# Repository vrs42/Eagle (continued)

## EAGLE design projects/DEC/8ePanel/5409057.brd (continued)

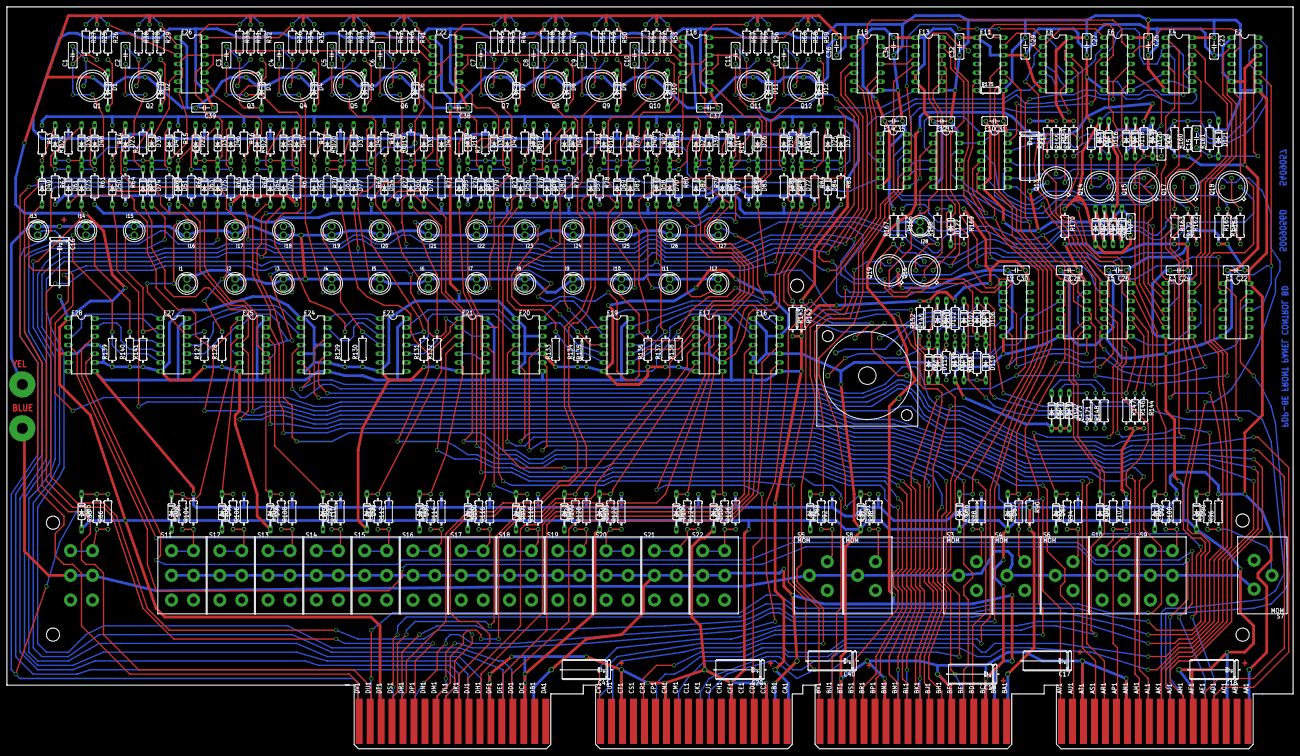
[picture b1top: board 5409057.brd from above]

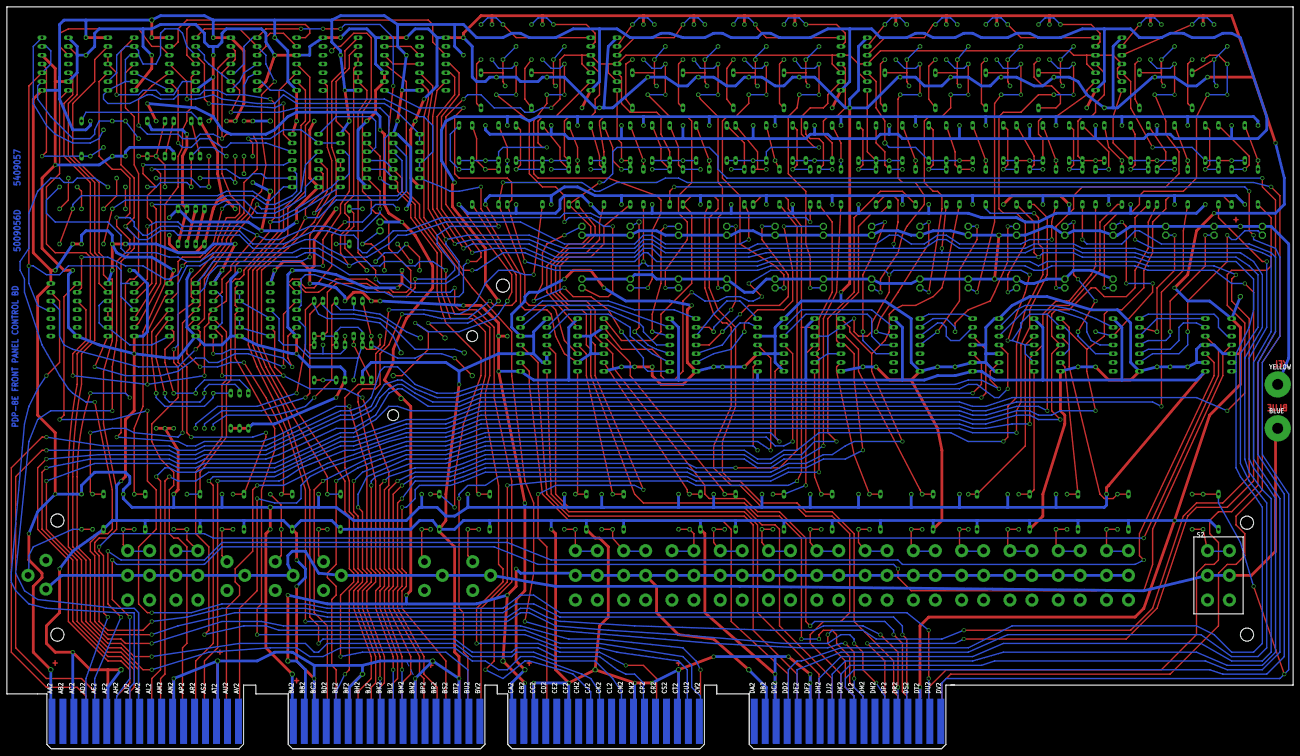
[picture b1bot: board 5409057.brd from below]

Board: 4 copper layers, 372.1 x 214.6 mm, 445 parts (3 on the bottom side), 319 nets.

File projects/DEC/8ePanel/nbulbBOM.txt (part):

Partlist exported from C:/Users/vrs/Documents/Eagle/projects/DEC/8ePanel/nbulb.sch at 6/27/2019 12:56:02 AM

Qty Value    Device            Package      Parts                                                                                                                                                                                                                                                                                                                                                                                                                                                                                                                                                                                          Description                                      
1            QUAD              EDGE-CON8    U$2                                                                                                                                                                                                                                                                                                                                                                                                                                                                                                                                                                                            Quad-Height DEC board                            
19  .01uF    C-US050-025X075   C050-025X075 C21, C22, C23, C24, C25, C26, C27, C28, C29, C30, C31, C32, C33, C34, C35, C36, C37, C38, C39                                                                                                                                                                                                                                                                                                                                                                                                                                                                                                  CAPACITOR, American symbol                       
22  1.5K     R-US_0207/10      0207/10      R85, R86, R87, R89, R91, R93, R95, R97, R99, R101, R103, R105, R107, R109, R111, R113, R115, R117, R119, R121, R123, R125                                                                                                                                                                                                                                                                                                                                                                                                                                                                      RESISTOR, American symbol                        
2   100      R-US_0207/10      0207/10      R154, R169                                                                                                                                                                                                                                                                                                                                                                                                                                                                                                                                                                                     RESISTOR, American symbol                        
1   150      R-US_0207/10      0207/10      R156                                                                                                                                                                                                                                                                                                                                                                                                                                                                                                                                                                                           RESISTOR, American symbol                        
15  15K      R-US_0207/10      0207/10      R1, R2, R3, R4, R5, R6, R7, R8, R9, R10, R11, R12, R158, R159, R160                                                                                                                                                                                                                                                                                                                                                                                                                                                                                                                            RESISTOR, American symbol                        
1   1800     R-US_0207/10      0207/10      R161                                                                                                                                                                                                                                                                                                                                                                                                                                                                                                                                                                                           RESISTOR, American symbol                        
6   1K       R-US_0207/10      0207/10      R149, R150, R153, R155, R166, R168                                                                                                                                                                                                                                                                                                                                                                                                                                                                                                                                                             RESISTOR, American symbol                        
2   1N4153   1N4148DO35-10     DO35-10      D120, D130                                                                                                                                                                                                                                                                                                                                                                                                                                                                                                                                                                                     DIODE                                            
114 1N4154   1N4148DO35-10     DO35-10      D1, D2, D3, D4, D5, D6, D7, D8, D9, D10, D11, D12, D13, D14, D15, D16, D17, D18, D19, D20, D21, D22, D23, D24, D25, D26, D27, D28, D29, D30, D31, D32, D33, D34, D35, D36, D37, D38, D39, D40, D41, D42, D43, D44, D45, D46, D47, D48, D49, D50, D51, D52, D53, D54, D55, D56, D57, D58, D59, D60, D61, D62, D63, D64, D65, D66, D67, D68, D69, D70, D71, D72, D73, D74, D75, D76, D77, D78, D79, D80, D81, D82, D83, D84, D85, D86, D87, D88, D89, D90, D91, D92, D93, D94, D95, D96, D97, D98, D99, D100, D101, D102, D103, D104, D105, D109, D116, D117, D118, D119, D121, D122, D127, D128 DIODE                                            
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
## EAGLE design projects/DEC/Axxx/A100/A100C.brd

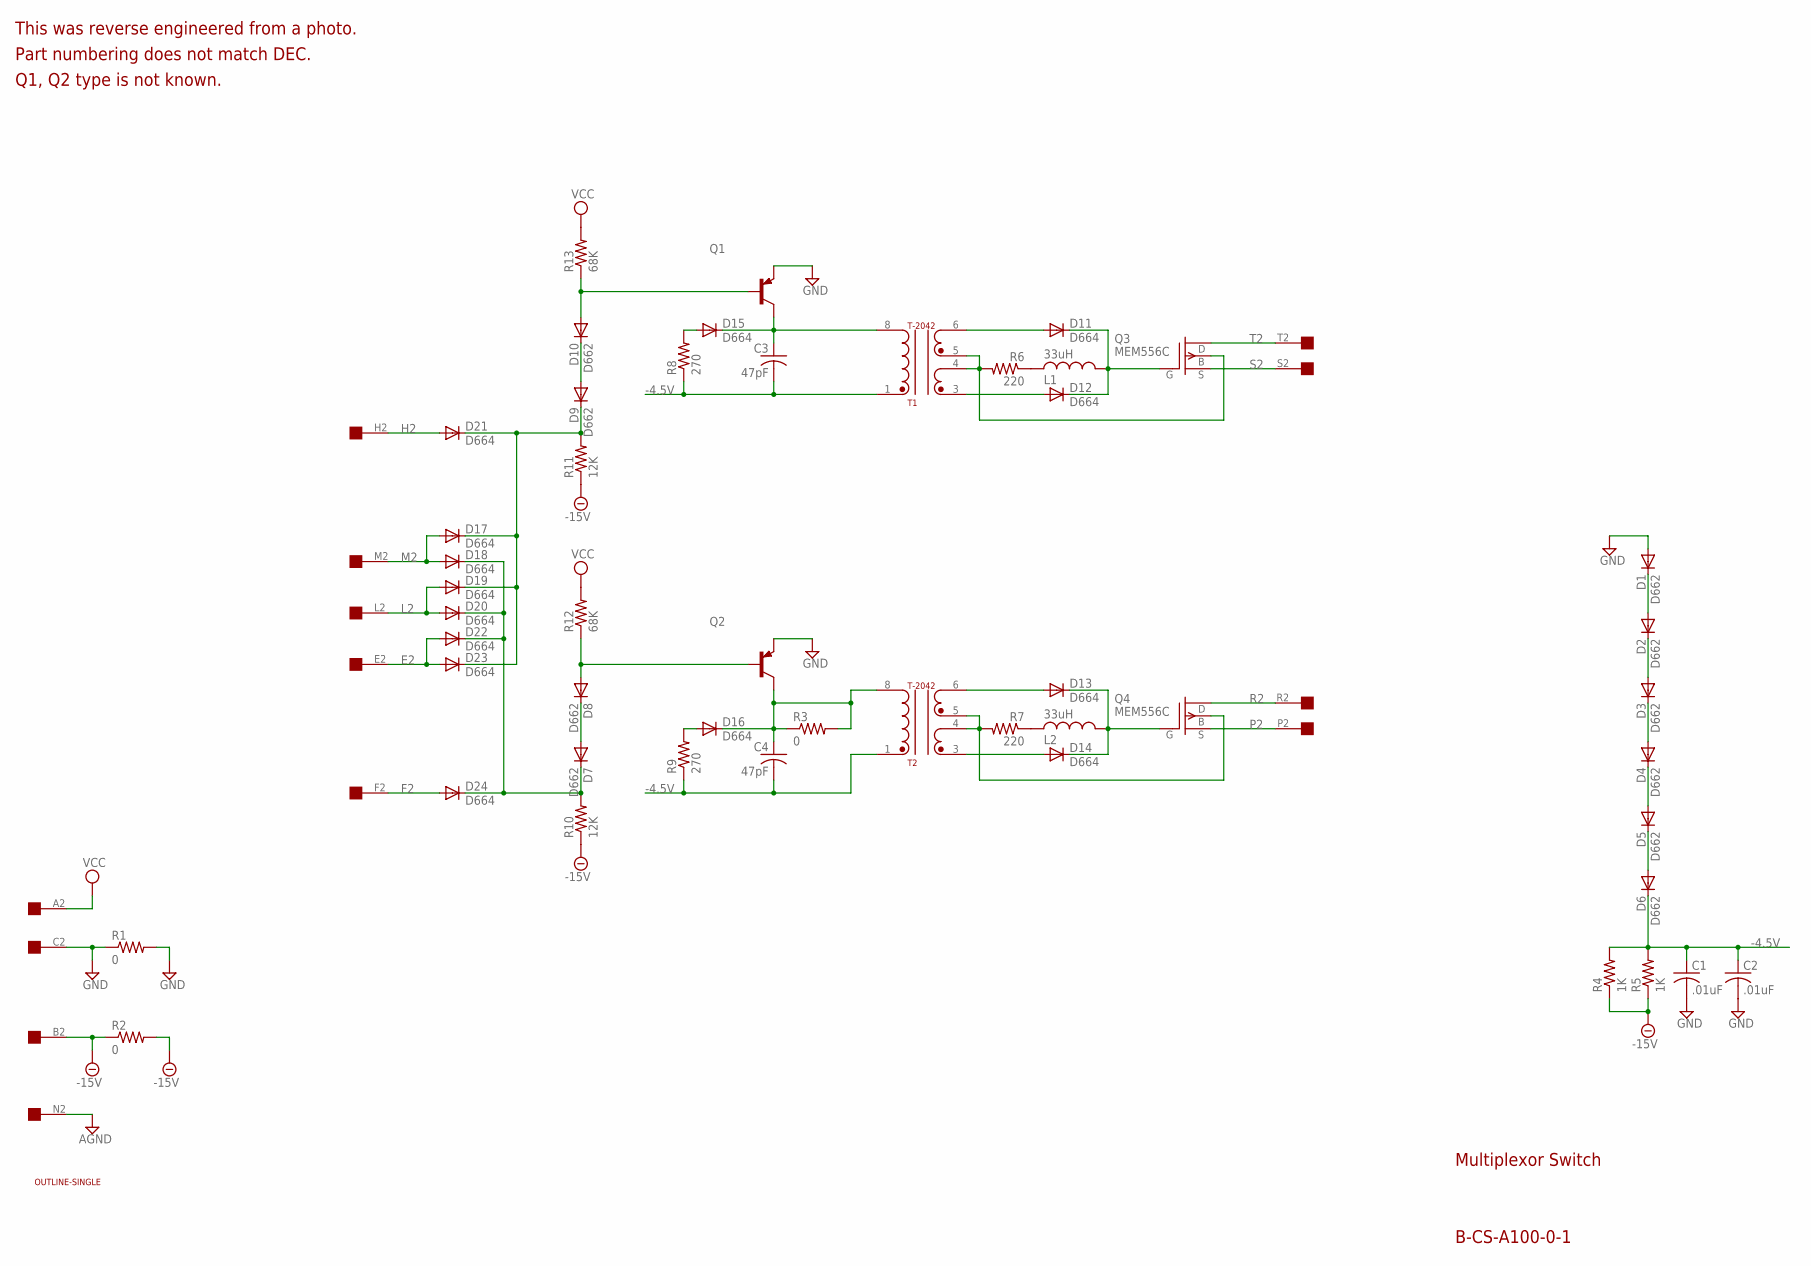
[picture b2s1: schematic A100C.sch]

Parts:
C1, C2: .01uF; C063-025X075
C3, C4: 47pF; C063-025X075
D1, D2, D3, D4, D5, D6, D7, D8, D9, D10: D662; DO35-10
D11, D12, D13, D14, D15, D16, D17, D18, D19, D20, D21, D22, D23, D24: D664; DO35-10
L1, L2: 33uH; 0207/15
Q1, Q2: -PNP-TO5; TO5
Q3, Q4: MEM556C; TO72
R1, R2, R3: 0; 0207/10
R4, R5: 1K; 0207/10
R6, R7: 220; 0207/10
R8, R9: 270; 0207/10
R10, R11: 12K; 0207/10
R12, R13: 68K; 0207/10
T1, T2: T-2042; TRANSFORMER6C
U$1: OUTLINE-SINGLE; SINGLE
U$2: EDGE-1; EDGE-CON1

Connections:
-4.5V: C1.1, C2.1, C3.2, C4.2, D6.C, R4.2, R5.2, R8.1, R9.1, T1.1 (3), T2.1 (3)
-15V: R2.1, R2.2, R4.1, R5.1, R10.1, R11.1, U$2.B2
AGND: U$2.N2
E2: D22.A, D23.A, U$2.E2
F2: D24.A, U$2.F2
GND: C1.2, C2.2, D1.A, Q1.1 (E), Q2.1 (E), R1.1, R1.2, U$2.C2
H2: D21.A, U$2.H2
L2: D19.A, D20.A, U$2.L2
M2: D17.A, D18.A, U$2.M2
unnamed: D1.C, D2.A
unnamed: D2.C, D3.A
unnamed: D3.C, D4.A
unnamed: D4.C, D5.A
unnamed: D5.C, D6.A
unnamed: C4.1, D16.C, Q2.3 (C), R3.1, R3.2, T2.8 (4)
unnamed: D9.C, D17.C, D19.C, D21.C, D23.C, R11.2
unnamed: D7.C, D18.C, D20.C, D22.C, D24.C, R10.2
unnamed: D7.A, D8.C
unnamed: D9.A, D10.C
unnamed: D8.A, Q2.2 (B), R12.1
unnamed: D10.A, Q1.2 (B), R13.1
unnamed: C3.1, D15.C, Q1.3 (C), T1.8 (4)
unnamed: D15.A, R8.2
unnamed: D16.A, R9.2
unnamed: Q3.4 (B), R6.2, T1.4 (5), T1.5 (1)
unnamed: L1.2, R6.1
unnamed: L2.2, R7.1
unnamed: D11.C, D12.C, L1.1, Q3.1 (G)
unnamed: D13.C, D14.C, L2.1, Q4.1 (G)
unnamed: Q4.4 (B), R7.2, T2.4 (5), T2.5 (1)
unnamed: D12.A, T1.3 (2)
unnamed: D11.A, T1.6
unnamed: D14.A, T2.3 (2)
unnamed: D13.A, T2.6
P2: Q4.3 (S), U$2.P2
R2: Q4.2 (D), U$2.R2
S2: Q3.3 (S), U$2.S2
T2: Q3.2 (D), U$2.T2
VCC: R12.2, R13.2, U$2.A2

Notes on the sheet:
Multiplexor Switch
B-CS-A100-0-1
This was reverse engineered from a photo.
Part numbering does not match DEC.
Q1, Q2 type is not known.

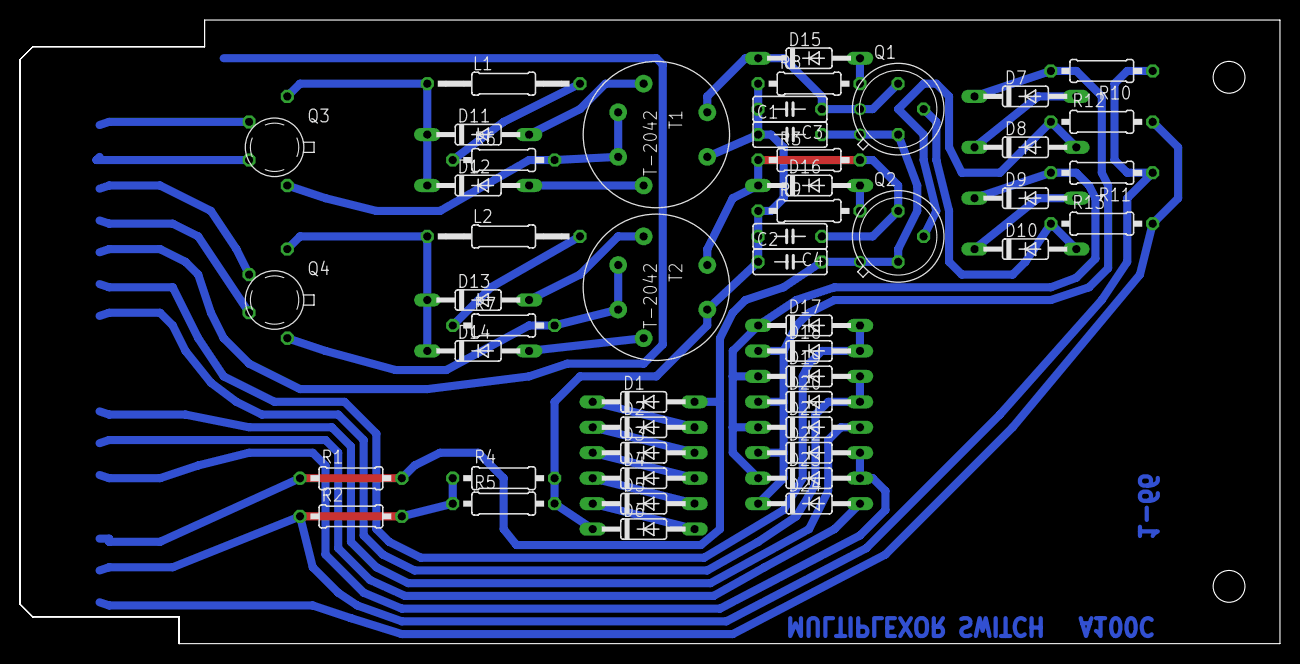
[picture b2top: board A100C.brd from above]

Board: 2 copper layers, 125.7 x 62.2 mm, 51 parts (0 on the bottom side), 38 nets.

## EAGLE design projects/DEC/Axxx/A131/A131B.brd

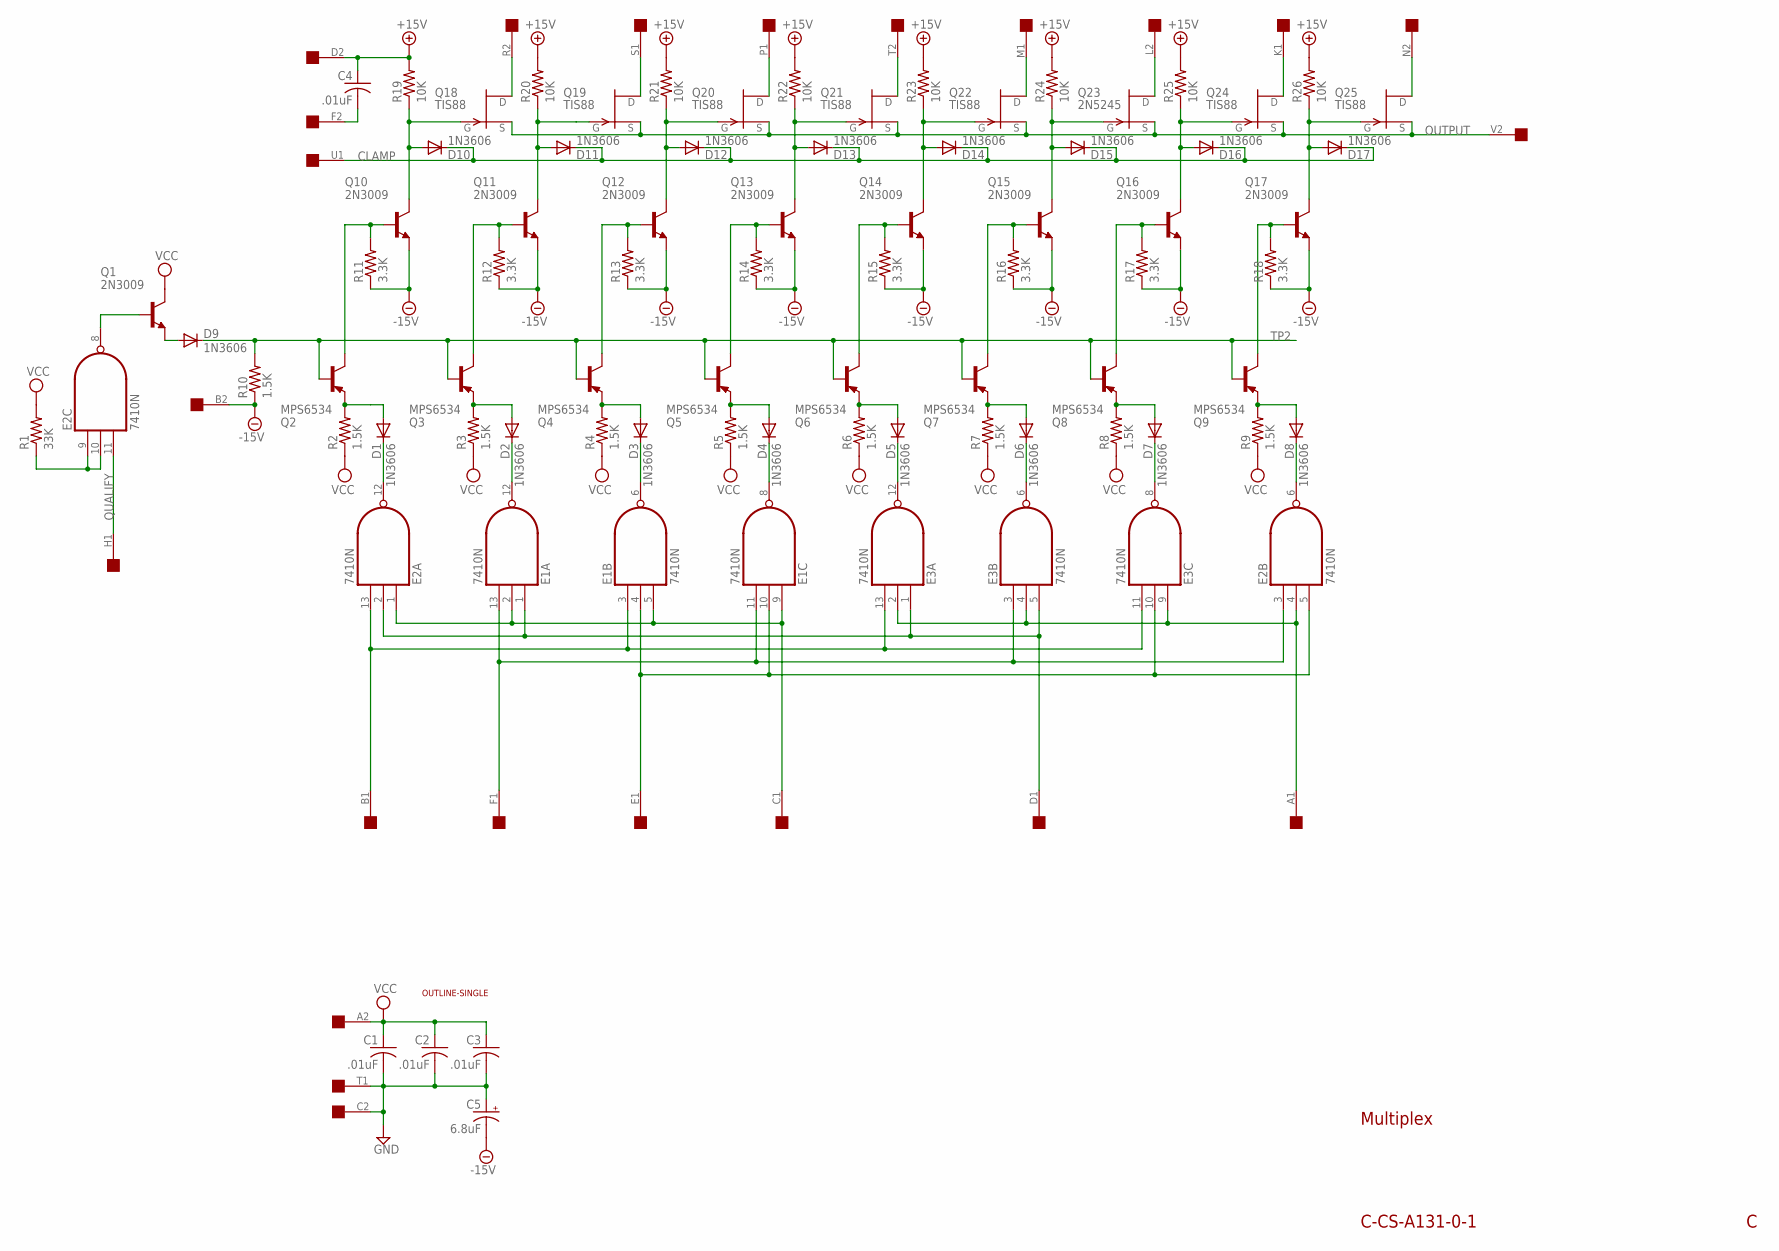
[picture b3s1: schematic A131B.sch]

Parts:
C1, C2, C3, C4: .01uF; C050-025X075
C5: 6.8uF; E12-8
D1, D2, D3, D4, D5, D6, D7, D8, D9, D10, D11, D12, D13, D14, D15, D16, D17: 1N3606; DO35-10
E1, E2, E3: 7410N; DIL14
Q1, Q10, Q11, Q12, Q13, Q14, Q15, Q16, Q17: 2N3009; TO5
Q2, Q3, Q4, Q5, Q6, Q7, Q8, Q9: MPS6534; TO5
Q18, Q19, Q20, Q21, Q22, Q24, Q25: TIS88; TO39
Q23: 2N5245; TO39
R1: 33K; 0207/10
R2, R3, R4, R5, R6, R7, R8, R9, R10: 1.5K; 0207/10
R11, R12, R13, R14, R15, R16, R17, R18: 3.3K; 0207/10
R19, R20, R21, R22, R23, R24, R25, R26: 10K; 0207/10
U$1: OUTLINE-SINGLE; SINGLE
U$2: SINGLE; EDGE-CON2

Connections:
+15V: C4.1, R19.2, R20.2, R21.2, R22.2, R23.2, R24.2, R25.2, R26.2, U$2.D2
-15V: C5.-, Q10.1 (E), Q11.1 (E), Q12.1 (E), Q13.1 (E), Q14.1 (E), Q15.1 (E), Q16.1 (E), Q17.1 (E), R10.1, R11.1, R12.1, R13.1, R14.1, R15.1, R16.1, R17.1, R18.1, U$2.B2
CLAMP: D10.C, D11.C, D12.C, D13.C, D14.C, D15.C, D16.C, D17.C, U$2.U1
GND: C1.2, C2.2, C3.2, C5.+, E1.7 (GND), E2.7 (GND), E3.7 (GND), U$2.C2, U$2.T1
unnamed: E2.9 (I0), E2.10 (I1), R1.1
unnamed: D10.A, Q10.3 (C), Q18.3 (G), R19.1
unnamed: D12.A, Q12.3 (C), Q20.3 (G), R21.1
unnamed: D13.A, Q13.3 (C), Q21.3 (G), R22.1
unnamed: D14.A, Q14.3 (C), Q22.3 (G), R23.1
unnamed: D15.A, Q15.3 (C), Q23.3 (G), R24.1
unnamed: D16.A, Q16.3 (C), Q24.3 (G), R25.1
unnamed: D17.A, Q17.3 (C), Q25.3 (G), R26.1
unnamed: Q18.2 (D), U$2.R2
unnamed: Q19.2 (D), U$2.S1
unnamed: Q20.2 (D), U$2.P1
unnamed: Q21.2 (D), U$2.T2
unnamed: Q22.2 (D), U$2.M1
unnamed: Q23.2 (D), U$2.L2
unnamed: Q24.2 (D), U$2.K1
unnamed: Q25.2 (D), U$2.N2
unnamed: C4.2, U$2.F2
unnamed: Q2.3 (C), Q10.2 (B), R11.2
unnamed: Q3.3 (C), Q11.2 (B), R12.2
unnamed: Q4.3 (C), Q12.2 (B), R13.2
unnamed: Q5.3 (C), Q13.2 (B), R14.2
unnamed: Q6.3 (C), Q14.2 (B), R15.2
unnamed: Q9.3 (C), Q17.2 (B), R18.2
unnamed: Q8.3 (C), Q16.2 (B), R17.2
unnamed: Q7.3 (C), Q15.2 (B), R16.2
unnamed: D1.A, Q2.1 (E), R2.2
unnamed: D2.A, Q3.1 (E), R3.2
unnamed: D3.A, Q4.1 (E), R4.2
unnamed: D4.A, Q5.1 (E), R5.2
unnamed: D5.A, Q6.1 (E), R6.2
unnamed: D6.A, Q7.1 (E), R7.2
unnamed: D7.A, Q8.1 (E), R8.2
unnamed: D8.A, Q9.1 (E), R9.2
unnamed: E2.8 (O), Q1.2 (B)
unnamed: D9.A, Q1.1 (E)
unnamed: D1.C, E2.12 (O)
unnamed: D2.C, E1.12 (O)
unnamed: D3.C, E1.6 (O)
unnamed: D4.C, E1.8 (O)
unnamed: D5.C, E3.12 (O)
unnamed: D6.C, E3.6 (O)
unnamed: D7.C, E3.8 (O)
unnamed: D8.C, E2.6 (O)
unnamed: E1.3 (I0), E2.13 (I2), E3.11 (I2), E3.13 (I2), U$2.B1
unnamed: E1.11 (I2), E1.13 (I2), E2.3 (I0), E3.3 (I0), U$2.F1
unnamed: E1.4 (I1), E1.10 (I1), E2.5 (I2), E3.10 (I1), U$2.E1
unnamed: E1.2 (I1), E1.5 (I2), E1.9 (I0), E2.1 (I0), U$2.C1
unnamed: D11.A, Q11.3 (C), Q19.3 (G), R20.1
unnamed: E2.4 (I1), E3.2 (I1), E3.4 (I1), E3.9 (I0), U$2.A1
unnamed: E1.1 (I0), E2.2 (I1), E3.1 (I0), E3.5 (I2), U$2.D1
OUTPUT: Q18.1 (S), Q19.1 (S), Q20.1 (S), Q21.1 (S), Q22.1 (S), Q23.1 (S), Q24.1 (S), Q25.1 (S), U$2.V2
QUALIFY: E2.11 (I2), U$2.H1
TP2: D9.C, Q2.2 (B), Q3.2 (B), Q4.2 (B), Q5.2 (B), Q6.2 (B), Q7.2 (B), Q8.2 (B), Q9.2 (B), R10.2
VCC: C1.1, C2.1, C3.1, E1.14 (VCC), E2.14 (VCC), E3.14 (VCC), Q1.3 (C), R1.2, R2.1, R3.1, R4.1, R5.1, R6.1, R7.1, R8.1, R9.1, U$2.A2

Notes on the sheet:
C-CS-A131-0-1
Multiplex

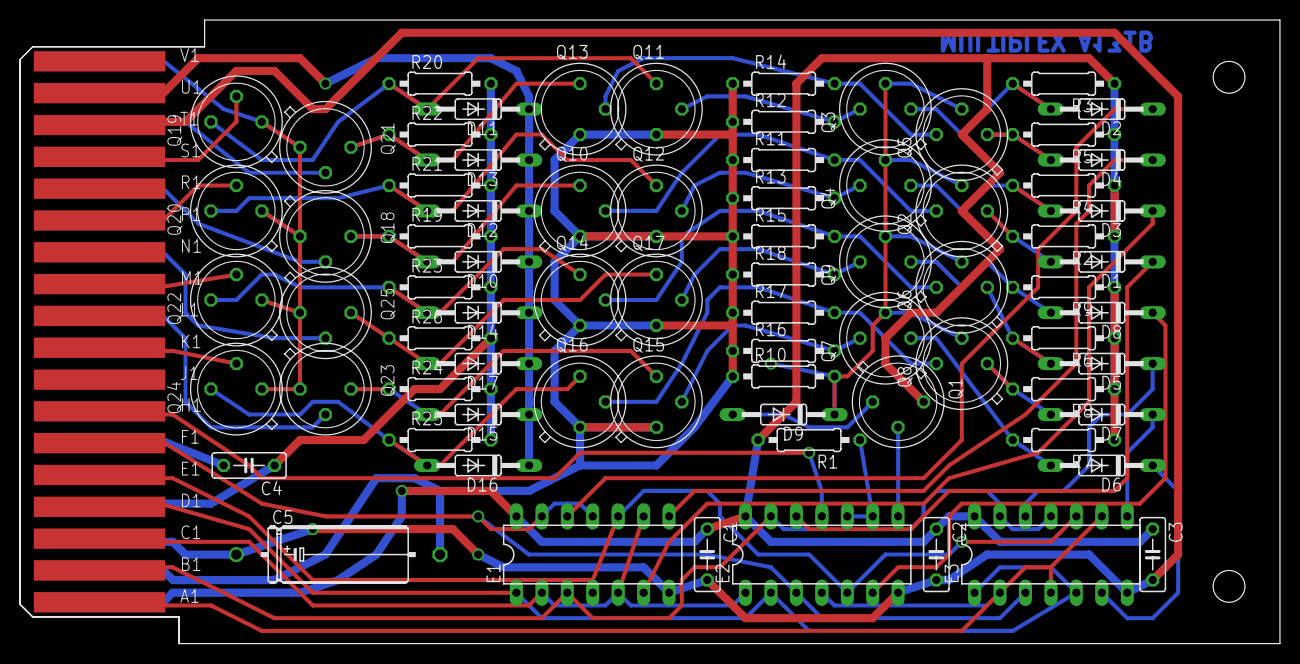
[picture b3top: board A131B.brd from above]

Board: 2 copper layers, 125.7 x 62.2 mm, 78 parts (0 on the bottom side), 58 nets.
